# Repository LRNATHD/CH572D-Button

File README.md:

# CH572D-Button
battery powered ch572d connected to a single button for optimal presses

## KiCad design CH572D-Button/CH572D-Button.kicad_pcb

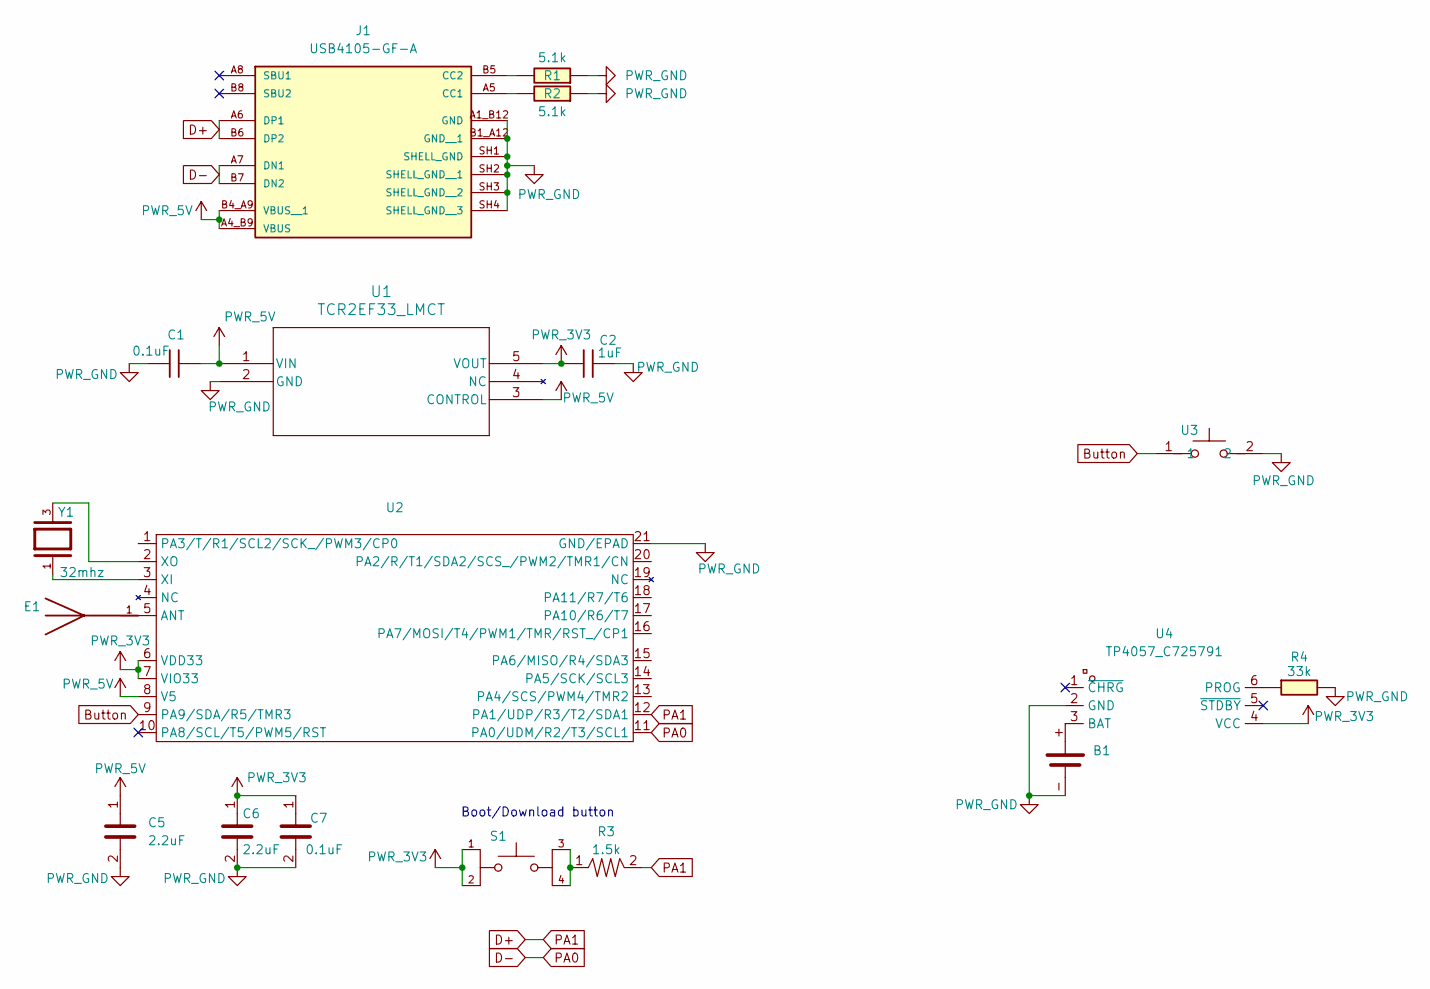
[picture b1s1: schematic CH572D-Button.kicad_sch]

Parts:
B1: supersmallbattery
C1, C7: 0.1uF; C_0603
C2: 1uF; C_0603
C5, C6: 2.2uF; C_0603
E1: AMCA31-2R450G-S1F-T3; ANT-F-1-2.4G-1.6mmFR4-WCH; PARTREV 03-21-19
J1: USB4105-GF-A; usbc; PARTREV B4
R1, R2: 5.1k; R_0603
R3: 1.5k; R_0603
R4: 33k; 0603
S1: TL3365AF180QG; button; PARTREV A
U1: TCR2EF33_LMCT; voltage regulator
U2: CH572D
U3: CPG151101D01; SW-TH_CPG151101D9X; LCSC Part C49234238
U4: TP4057_C725791; SOT-23-6_L2.9-W1.6-P0.95-LS2.8-BR; LCSC Part C725791
Y1: 32mhz; 32mhz crystal; PARTREV N/A

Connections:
Button: U2.9 (PA9/SDA/R5/TMR3), U3.1
D+: J1.A6 (DP1), J1.B6 (DP2), R3.2, U2.12 (PA1/UDP/R3/T2/SDA1)
D-: J1.A7 (DN1), J1.B7 (DN2), U2.11 (PA0/UDM/R2/T3/SCL1)
unnamed: J1.A5 (CC1), R2.1
unnamed: J1.B5 (CC2), R1.1
unnamed: R3.1, S1.3, S1.4
unnamed: E1.1, U2.5 (ANT)
unnamed: U2.3 (XI), Y1.1
unnamed: U2.2 (XO), Y1.3
unnamed: B1.+, U4.3 (BAT)
unnamed: R4.2, U4.6 (PROG)
PWR_3V3: C2.1, C6.1, C7.1, S1.1, S1.2, U1.5 (VOUT), U2.6 (VDD33), U2.7 (VIO33), U4.4 (VCC)
PWR_5V: C1.2, C5.1, J1.A4_B9 (VBUS), J1.B4_A9 (VBUS__1), U1.1 (VIN), U1.3 (CONTROL), U2.8 (V5)
PWR_GND: B1.-, C1.1, C2.2, C5.2, C6.2, C7.2, E1.0, J1.A1_B12 (GND), J1.B1_A12 (GND__1), J1.SH1 (SHELL_GND), J1.SH2 (SHELL_GND__1), J1.SH3 (SHELL_GND__2), J1.SH4 (SHELL_GND__3), R1.2, R2.2, R4.1, U1.2 (GND), U2.21 (GND/EPAD), U3.2, U4.2 (GND)

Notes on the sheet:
Boot/Download button

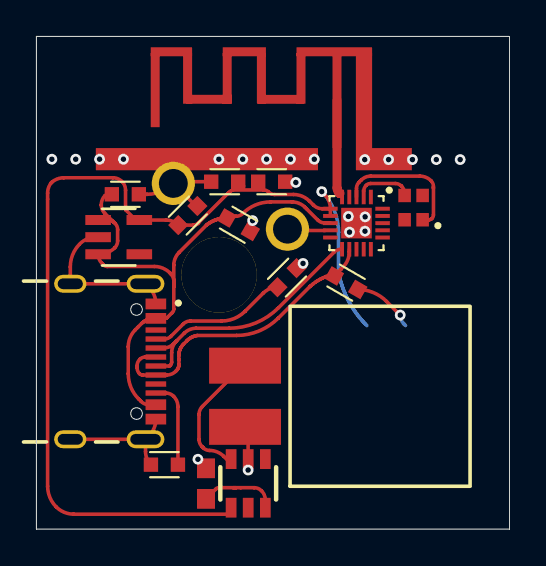
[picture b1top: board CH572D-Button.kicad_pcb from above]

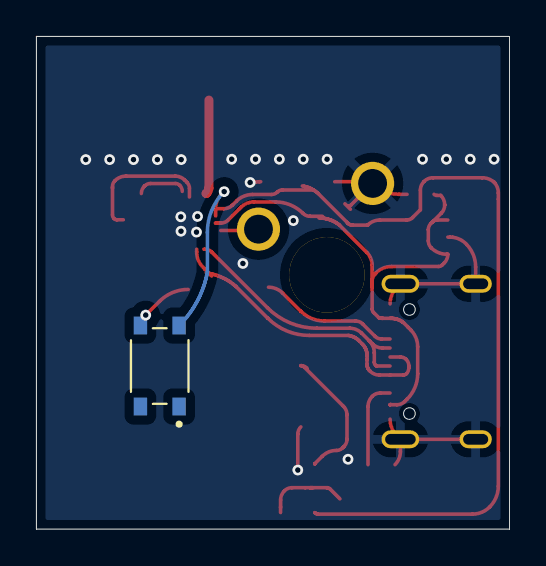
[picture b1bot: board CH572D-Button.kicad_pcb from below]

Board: 2 copper layers, 26.3 x 27.4 mm, 18 parts (2 on the bottom side), 14 nets.

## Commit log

2025-10-17 started just put the micro down
2025-11-30 button done hope it works not requires enig plating for the atnenana
